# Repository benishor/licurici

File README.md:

# licurici
Simple SMD transistor based astable multivibrator in KiCad.

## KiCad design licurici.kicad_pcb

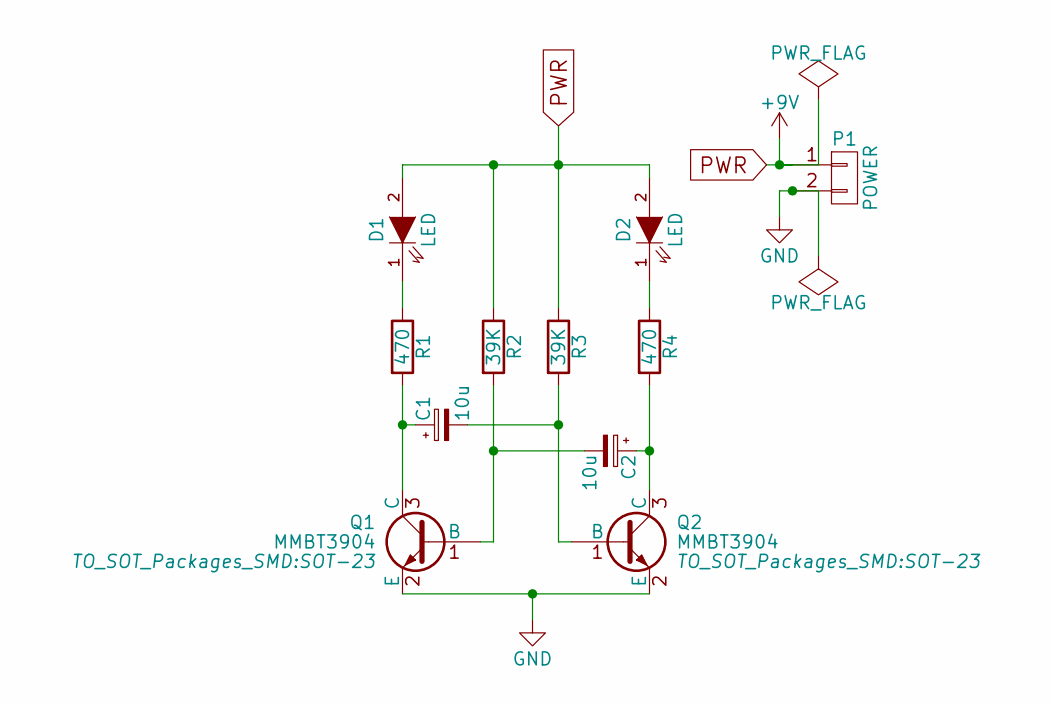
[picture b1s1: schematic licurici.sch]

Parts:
C1, C2: 10u; c_elec_4x4.5
D1, D2: LED; LED-3MM
P1: POWER; Pin_Header_Straight_1x02
Q1, Q2: MMBT3904; SOT-23
R1, R4: 470; R_1206_HandSoldering
R2, R3: 39K; R_1206_HandSoldering

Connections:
GND: P1.2, Q1.2 (E), Q2.2 (E)
unnamed: C1.1, Q1.3 (C), R1.2
unnamed: C1.2, Q2.1 (B), R3.2
unnamed: C2.1, Q2.3 (C), R4.2
unnamed: C2.2, Q1.1 (B), R2.2
unnamed: D1.1 (K), R1.1
unnamed: D2.1 (K), R4.1
PWR: D1.2 (A), D2.2 (A), P1.1, R2.1, R3.1

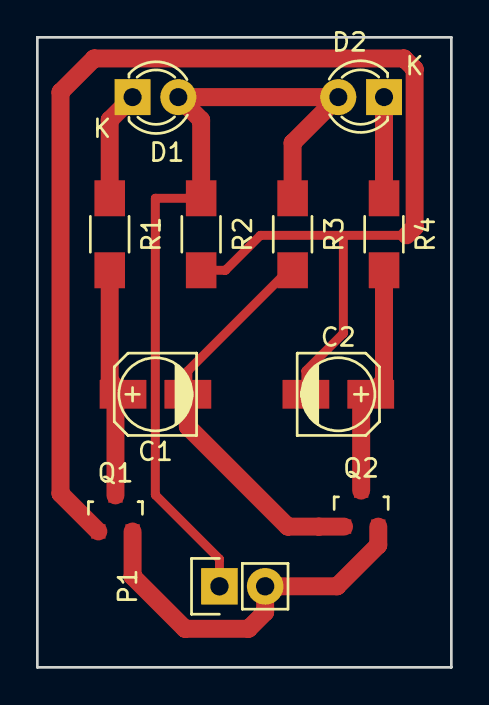
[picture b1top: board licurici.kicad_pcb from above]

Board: 2 copper layers, 23.0 x 35.0 mm, 11 parts (0 on the bottom side), 8 nets.

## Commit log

2016-10-09 Initial import
